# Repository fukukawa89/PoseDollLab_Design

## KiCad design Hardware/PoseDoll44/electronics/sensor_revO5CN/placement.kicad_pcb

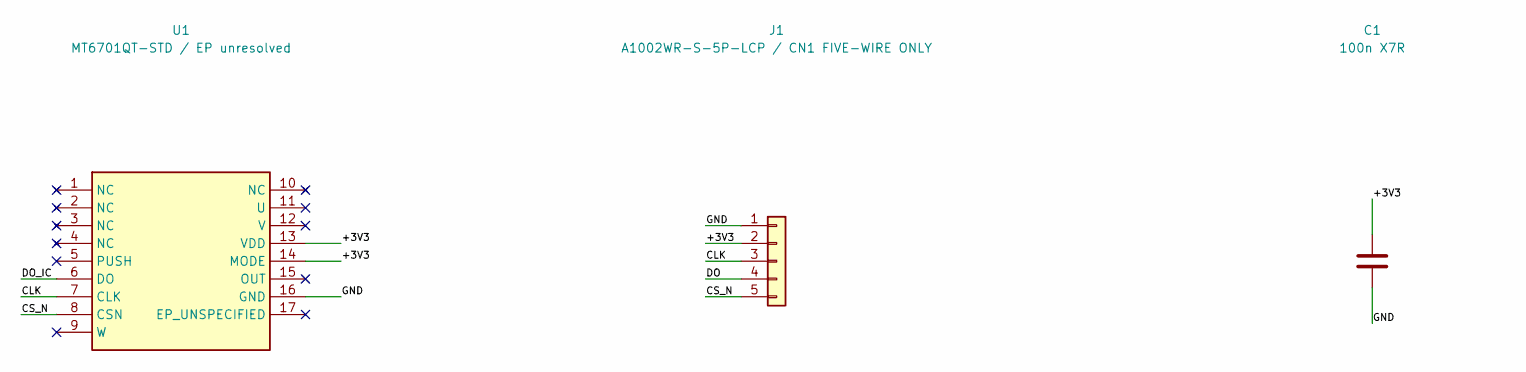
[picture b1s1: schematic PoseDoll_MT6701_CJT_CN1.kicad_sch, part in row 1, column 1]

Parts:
C1: 100n X7R; C_0603_1608Metric
C2: 10u bulk; derating pending; C_0805_2012Metric
J1: A1002WR-S-5P-LCP / CN1 FIVE-WIRE ONLY; CJT_A1002WR_S_5P_LCP
R1: 33R source damping candidate; R_0603_1608Metric
R2: 10k CS safe high; R_0603_1608Metric
U1: MT6701QT-STD / EP unresolved; MT6701QT_QFN16_EP_UNSPECIFIED

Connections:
/+3V3: C1.1, C2.1, J1.2, R2.1, U1.13 (VDD), U1.14 (MODE)
/CLK: J1.3, U1.7 (CLK)
/CS_N: J1.5, R2.2, U1.8 (CSN)
/DO: J1.4, R1.2
/DO_IC: R1.1, U1.6 (DO)
/GND: C1.2, C2.2, J1.1, U1.16 (GND)

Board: 2 copper layers, 6 parts (1 on the bottom side), 6 nets, no tracks yet.

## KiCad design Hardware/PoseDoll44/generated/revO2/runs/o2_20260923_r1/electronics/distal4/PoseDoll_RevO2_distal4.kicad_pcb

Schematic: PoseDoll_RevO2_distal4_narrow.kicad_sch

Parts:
C26, C27, C28, C29: 100n X7R; C_0603_1608Metric
C50: 1u X7R; C_0603_1608Metric
J16: P6 sensor / CS GPIO8; JST_SH_BM06B-SRSS-TB_1x06-1MP_P1.00mm_Vertical
J17: P7 sensor / CS GPIO9; JST_SH_BM06B-SRSS-TB_1x06-1MP_P1.00mm_Vertical
J18: P8 sensor / CS GPIO10; JST_SH_BM06B-SRSS-TB_1x06-1MP_P1.00mm_Vertical
J19: P9 sensor / CS GPIO14; JST_SH_BM06B-SRSS-TB_1x06-1MP_P1.00mm_Vertical
J50: BM14B-SRSS-TB / SHR-14V-S / SSH-003T-P0.2-H; JST_SH_BM14B-SRSS-TB_1x14-1MP_P1.00mm_Vertical
R160, R161, R162, R170, R171, R172, R180, R181, R182, R190, R191, R192: 100R; R_0603_1608Metric
R163, R167, R173, R177, R183, R187, R193, R197: 10k; R_0603_1608Metric
R164, R165, R174, R175, R184, R185, R194, R195: 47k; R_0603_1608Metric
R166, R176, R186, R196: 100k; R_0603_1608Metric
R500: 100R return source damping candidate; R_0603_1608Metric
U16, U17, U18, U19: SN74LVC125ABQAR; DHWQFN-14-1EP_2.5x3mm_P0.5mm_EP1x1.5mm

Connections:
/+3V3: C26.1, C27.1, C28.1, C29.1, C50.1, J16.2, J17.2, J18.2, J19.2, J50.13, J50.14, R163.1, R167.1, R173.1, R177.1, R183.1, R187.1, R193.1, R197.1, U16.14 (VCC), U17.14 (VCC), U18.14 (VCC), U19.14 (VCC)
/CS6_REMOTE: J50.7, R163.2, U16.1 (1OE_N), U16.4 (2OE_N), U16.10 (3OE_N), U16.12 (4A)
/CS7_REMOTE: J50.8, R173.2, U17.1 (1OE_N), U17.4 (2OE_N), U17.10 (3OE_N), U17.12 (4A)
/CS8_REMOTE: J50.10, R183.2, U18.1 (1OE_N), U18.4 (2OE_N), U18.10 (3OE_N), U18.12 (4A)
/CS9_REMOTE: J50.11, R193.2, U19.1 (1OE_N), U19.4 (2OE_N), U19.10 (3OE_N), U19.12 (4A)
/GND: C26.2, C27.2, C28.2, C29.2, C50.2, J16.1, J17.1, J18.1, J19.1, J50.1, J50.3, J50.5, J50.9, J50.12, R164.2, R165.2, R166.2, R174.2, R175.2, R176.2, R184.2, R185.2, R186.2, R194.2, R195.2, R196.2, U16.7 (GND), U16.13 (4OE_N), U16.15 (EP_GND), U17.7 (GND), U17.13 (4OE_N), U17.15 (EP_GND), U18.7 (GND), U18.13 (4OE_N), U18.15 (EP_GND), U19.7 (GND), U19.13 (4OE_N), U19.15 (EP_GND)
/LINK_MISO: J50.6, R500.2
/LINK_MOSI: J50.4, U16.5 (2A), U17.5 (2A), U18.5 (2A), U19.5 (2A)
/LINK_SCK: J50.2, U16.2 (1A), U17.2 (1A), U18.2 (1A), U19.2 (1A)
/MISO_REMOTE_DRV: R500.1, U16.8 (3Y), U17.8 (3Y), U18.8 (3Y), U19.8 (3Y)
/P6_CS: J16.6, R162.2, R167.2
/P6_CS_DRV: R162.1, U16.11 (4Y)
/P6_MISO: J16.5, R166.1, U16.9 (3A)
/P6_MOSI: J16.4, R161.2, R165.1
/P6_MOSI_DRV: R161.1, U16.6 (2Y)
/P6_SCK: J16.3, R160.2, R164.1
/P6_SCK_DRV: R160.1, U16.3 (1Y)
/P7_CS: J17.6, R172.2, R177.2
/P7_CS_DRV: R172.1, U17.11 (4Y)
/P7_MISO: J17.5, R176.1, U17.9 (3A)
/P7_MOSI: J17.4, R171.2, R175.1
/P7_MOSI_DRV: R171.1, U17.6 (2Y)
/P7_SCK: J17.3, R170.2, R174.1
/P7_SCK_DRV: R170.1, U17.3 (1Y)
/P8_CS: J18.6, R182.2, R187.2
/P8_CS_DRV: R182.1, U18.11 (4Y)
/P8_MISO: J18.5, R186.1, U18.9 (3A)
/P8_MOSI: J18.4, R181.2, R185.1
/P8_MOSI_DRV: R181.1, U18.6 (2Y)
/P8_SCK: J18.3, R180.2, R184.1
/P8_SCK_DRV: R180.1, U18.3 (1Y)
/P9_CS: J19.6, R192.2, R197.2
/P9_CS_DRV: R192.1, U19.11 (4Y)
/P9_MISO: J19.5, R196.1, U19.9 (3A)
/P9_MOSI: J19.4, R191.2, R195.1
/P9_MOSI_DRV: R191.1, U19.6 (2Y)
/P9_SCK: J19.3, R190.2, R194.1
/P9_SCK_DRV: R190.1, U19.3 (1Y)

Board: 4 copper layers, 47 parts (42 on the bottom side), 38 nets, no tracks yet.

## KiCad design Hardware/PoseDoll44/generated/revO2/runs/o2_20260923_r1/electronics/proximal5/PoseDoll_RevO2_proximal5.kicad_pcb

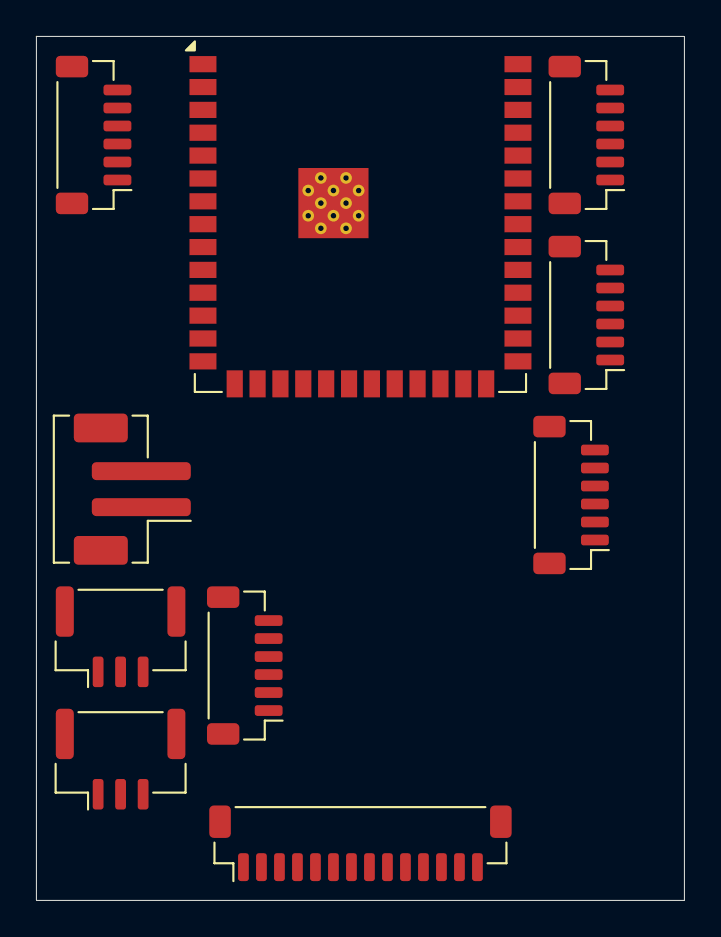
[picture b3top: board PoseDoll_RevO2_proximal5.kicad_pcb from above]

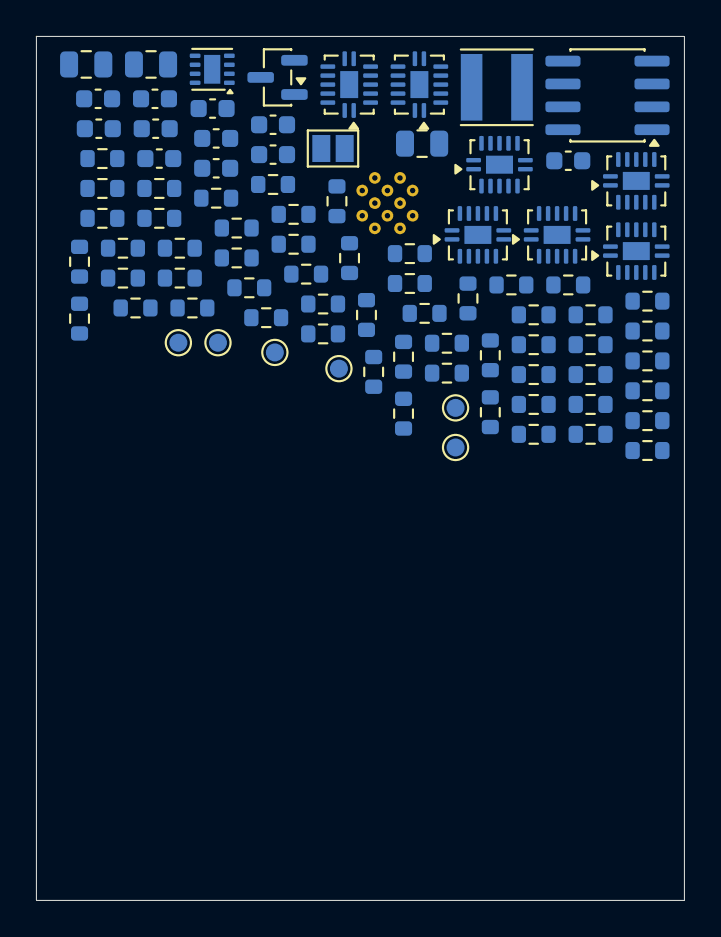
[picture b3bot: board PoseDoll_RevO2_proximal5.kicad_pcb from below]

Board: 4 copper layers, 36.0 x 48.0 mm, 98 parts (88 on the bottom side), 74 nets, no tracks yet.

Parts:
C1: 10u X5R 25V / CL21A106KAYNNNE; C_0805_2012Metric
C2, C4: 22u X5R 16V / CL21A226MOYNNNE; C_0805_2012Metric
C3, C5, C7, C21, C22, C23, C24, C25, C50, C51: 100n X7R; C_0603_1608Metric
C6: 1u X7R; C_0603_1608Metric
D1: PESD5V0S2BT,215; SOT-23
J1: 5V protected N3/N4 branch; not 12V qualified; JST_PH_B2B-PH-SM4-TB_1x02-1MP_P2.00mm_Vertical
J2: CAN IN / GND-L-H; JST_GH_BM03B-GHS-TBT_1x03-1MP_P1.25mm_Vertical
J3: CAN OUT / GND-L-H; JST_GH_BM03B-GHS-TBT_1x03-1MP_P1.25mm_Vertical
J11: P1 sensor / CS GPIO2; JST_SH_BM06B-SRSS-TB_1x06-1MP_P1.00mm_Vertical
J12: P2 sensor / CS GPIO4; JST_SH_BM06B-SRSS-TB_1x06-1MP_P1.00mm_Vertical
J13: P3 sensor / CS GPIO5; JST_SH_BM06B-SRSS-TB_1x06-1MP_P1.00mm_Vertical
J14: P4 sensor / CS GPIO6; JST_SH_BM06B-SRSS-TB_1x06-1MP_P1.00mm_Vertical
J15: P5 sensor / CS GPIO7; JST_SH_BM06B-SRSS-TB_1x06-1MP_P1.00mm_Vertical
J50: BM14B-SRSS-TB / SHR-14V-S / SSH-003T-P0.2-H; JST_SH_BM14B-SRSS-TB_1x14-1MP_P1.00mm_Vertical
JP1: CAN TERM: close endpoints only; SolderJumper-2_P1.3mm_Open_Pad1.0x1.5mm
L1: LSXND4040TKL2R2MDG / 2.2uH; L_Taiyo-Yuden_NR-40xx
R1, R2, R4, R113, R117, R123, R127, R133, R137, R143, R147, R153, R157, R526, R527, R528, R529: 10k; R_0603_1608Metric
R3, R116, R126, R136, R146, R156: 100k; R_0603_1608Metric
R5: 120R 1% 0.33W / CRCW0603120RFKEAHP; R_0603_1608Metric
R110, R111, R112, R120, R121, R122, R130, R131, R132, R140, R141, R142, R150, R151, R152: 100R; R_0603_1608Metric
R114, R115, R124, R125, R134, R135, R144, R145, R154, R155: 47k; R_0603_1608Metric
R500, R501, R502, R503, R510, R511: 100R source damping candidate; R_0603_1608Metric
R530: 0R option / direct tri-state return; R_0603_1608Metric
TP1: UART_TX; TestPoint_Pad_D1.0mm
TP2: UART_RX; TestPoint_Pad_D1.0mm
TP3: GND; TestPoint_Pad_D1.0mm
TP4: PG; TestPoint_Pad_D1.0mm
TP5: EN; TestPoint_Pad_D1.0mm
TP6: BOOT_N; TestPoint_Pad_D1.0mm
U1: ESP32-S3-WROOM-1-N8; ESP32-S3-WROOM-1_thermal030
U2: TPS62162DSGR; Texas_DSG0008A_WSON-8-1EP_2x2mm_P0.5mm_EP0.9x1.6mm
U3: TCAN332DR; SOIC-8_3.9x4.9mm_P1.27mm
U11, U12, U13, U14, U15, U50, U51: SN74LVC125ABQAR; DHWQFN-14-1EP_2.5x3mm_P0.5mm_EP1x1.5mm

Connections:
/+3V3: C2.1, C4.1, C5.1, C7.1, C21.1, C22.1, C23.1, C24.1, C25.1, C50.1, C51.1, J11.2, J12.2, J13.2, J14.2, J15.2, J50.13, J50.14, L1.2, R1.1, R2.1, R3.1, R4.1, R113.1, R117.1, R123.1, R127.1, R133.1, R137.1, R143.1, R147.1, R153.1, R157.1, R526.1, R527.1, R528.1, R529.1, U1.2, U2.6, U3.3, U11.14, U12.14, U13.14, U14.14, U15.14, U50.14, U51.10, U51.13, U51.14
/+5V_IN: C1.1, C3.1, J1.1, U2.2, U2.3
/BOOT_N: R2.2, TP6.1, U1.27
/CAN_H: D1.2, J2.3, J3.3, R5.1, U3.7
/CAN_L: D1.1, J2.2, J3.2, JP1.2, U3.6
/CAN_RX: U1.11, U3.4
/CAN_TX: R4.2, U1.10, U3.1
/CS1_MCU: R113.2, U1.38, U11.1, U11.4, U11.10, U11.12
/CS2_MCU: R123.2, U1.4, U12.1, U12.4, U12.10, U12.12
/CS3_MCU: R133.2, U1.5, U13.1, U13.4, U13.10, U13.12
/CS4_MCU: R143.2, U1.6, U14.1, U14.4, U14.10, U14.12
/CS5_MCU: R153.2, U1.7, U15.1, U15.4, U15.10, U15.12
/CS6_MCU: R526.2, U1.12, U50.9
/CS6_REMOTE: J50.7, R502.2
/CS6_REMOTE_DRV: R502.1, U50.8
/CS7_MCU: R527.2, U1.17, U50.12
/CS7_REMOTE: J50.8, R503.2
/CS7_REMOTE_DRV: R503.1, U50.11
/CS8_MCU: R528.2, U1.18, U51.2
/CS8_REMOTE: J50.10, R510.2
/CS8_REMOTE_DRV: R510.1, U51.3
/CS9_MCU: R529.2, U1.22, U51.5
/CS9_REMOTE: J50.11, R511.2
/CS9_REMOTE_DRV: R511.1, U51.6
/EN: C6.1, R1.2, TP5.1, U1.3
/GND: C1.2, C2.2, C3.2, C4.2, C5.2, C6.2, C7.2, C21.2, C22.2, C23.2, C24.2, C25.2, C50.2, C51.2, D1.3, J1.2, J2.1, J3.1, J11.1, J12.1, J13.1, J14.1, J15.1, J50.1, J50.3, J50.5, J50.9, J50.12, R114.2, R115.2, R116.2, R124.2, R125.2, R126.2, R134.2, R135.2, R136.2, R144.2, R145.2, R146.2, R154.2, R155.2, R156.2, TP3.1, U1.1, U1.40, U1.41, U2.1, U2.4, U2.5, U2.9, U3.2, U11.7, U11.13, U11.15, U12.7, U12.13, U12.15, U13.7, U13.13, U13.15, U14.7, U14.13, U14.15, U15.7, U15.13, U15.15, U50.1, U50.4, U50.7, U50.10, U50.13, U50.15, U51.1, U51.4, U51.7, U51.9, U51.12, U51.15
/LINK_MISO: J50.6, R530.1
/LINK_MOSI: J50.4, R501.2
/LINK_MOSI_DRV: R501.1, U50.6
/LINK_SCK: J50.2, R500.2
/LINK_SCK_DRV: R500.1, U50.3
/P1_CS: J11.6, R112.2, R117.2
/P1_CS_DRV: R112.1, U11.11
/P1_MISO: J11.5, R116.1, U11.9
/P1_MOSI: J11.4, R111.2, R115.1
/P1_MOSI_DRV: R111.1, U11.6
/P1_SCK: J11.3, R110.2, R114.1
/P1_SCK_DRV: R110.1, U11.3
/P2_CS: J12.6, R122.2, R127.2
/P2_CS_DRV: R122.1, U12.11
/P2_MISO: J12.5, R126.1, U12.9
/P2_MOSI: J12.4, R121.2, R125.1
/P2_MOSI_DRV: R121.1, U12.6
/P2_SCK: J12.3, R120.2, R124.1
/P2_SCK_DRV: R120.1, U12.3
/P3_CS: J13.6, R132.2, R137.2
/P3_CS_DRV: R132.1, U13.11
/P3_MISO: J13.5, R136.1, U13.9
/P3_MOSI: J13.4, R131.2, R135.1
/P3_MOSI_DRV: R131.1, U13.6
/P3_SCK: J13.3, R130.2, R134.1
/P3_SCK_DRV: R130.1, U13.3
/P4_CS: J14.6, R142.2, R147.2
/P4_CS_DRV: R142.1, U14.11
/P4_MISO: J14.5, R146.1, U14.9
/P4_MOSI: J14.4, R141.2, R145.1
/P4_MOSI_DRV: R141.1, U14.6
/P4_SCK: J14.3, R140.2, R144.1
/P4_SCK_DRV: R140.1, U14.3
/P5_CS: J15.6, R152.2, R157.2
/P5_CS_DRV: R152.1, U15.11
/P5_MISO: J15.5, R156.1, U15.9
/P5_MOSI: J15.4, R151.2, R155.1
/P5_MOSI_DRV: R151.1, U15.6
/P5_SCK: J15.3, R150.2, R154.1
/P5_SCK_DRV: R150.1, U15.3
/PG: R3.2, TP4.1, U2.8
/SPI_MISO: R530.2, U1.21, U11.8, U12.8, U13.8, U14.8, U15.8
/SPI_MOSI: U1.19, U11.5, U12.5, U13.5, U14.5, U15.5, U50.5
/SPI_SCK: U1.20, U11.2, U12.2, U13.2, U14.2, U15.2, U50.2
/SW_BUCK: L1.1, U2.7
/TERM_R: JP1.1, R5.2
/UART_RX: TP2.1, U1.36
/UART_TX: TP1.1, U1.37
